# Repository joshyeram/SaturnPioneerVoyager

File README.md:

# Saturn with Pioneer and Voyager

link to the build video: https://www.youtube.com/watch?v=A1N8exJrTmQ

# Saturn

With this keyboard, I wanted to experiment with the possibility of hot-swappable keyboards. In the current state of using machine sockets and pins, no one dares to hot-swap. And I wanted to fix that and come up with a universal microcontroller daughter board that you can simply swap around.

# Pioneer

Pioneer is a simple daughterboard that supports a pro-micro-like microcontroller and a simple switch (reset). You can use qmk to program it.

# Voyager

Voyager is a complicated daughterboard that supports a pro-micro-like microcontroller, either oled or nice!view, a battery, and two switches (reset and power). Because of this, it is very thick to support all the hardware. In this case, I decided to use a Supermini for cost reasons. However, a genuine nice!nano should work as well. For programming, zmk was used for Bluetooth. 

# PCB

All you need is one pcb for all the boards. This is because I designed the daughter boards to be in the corners of the board to save manufacturing costs. This is at the cost of needing to score and snap off each board.

The reason why this works is because all the connections are standardized

Also, I think I got really lucky with the auditor not checking the thin mouse bite. so you may need to increase the tab if they do not except it.

# Firmware
I have already compiled and posted the .hex (qmk) and build.yaml(zmk) in the firmware folder. However, if you would like to make it your own, I have posted the full source code of what I used as well. (There may be some refactoring issues but I think I got most of them. Let me know if there is anything to fix)

# Parts
The most important part of the whole build was the DB25 connectors. I had to edit the existing DB25 footprint to fit my DB25 pins. So, you might have to as well.
Here is the list of parts I used
- pcb
- db25 connectors from amazon
- promicro 
- nice!nano clone
- nice!view from typeractive.xyz (they are great btw)
-  holy panda clones
- silent honey peaches
- 3 pin switches
- 1n4148 diodes
- uv resin
- some wire for cs pin
- keycaps (cerakeys w)

# anything else
please ask me anything if you guys want to! it is joshyeram on most platforms.

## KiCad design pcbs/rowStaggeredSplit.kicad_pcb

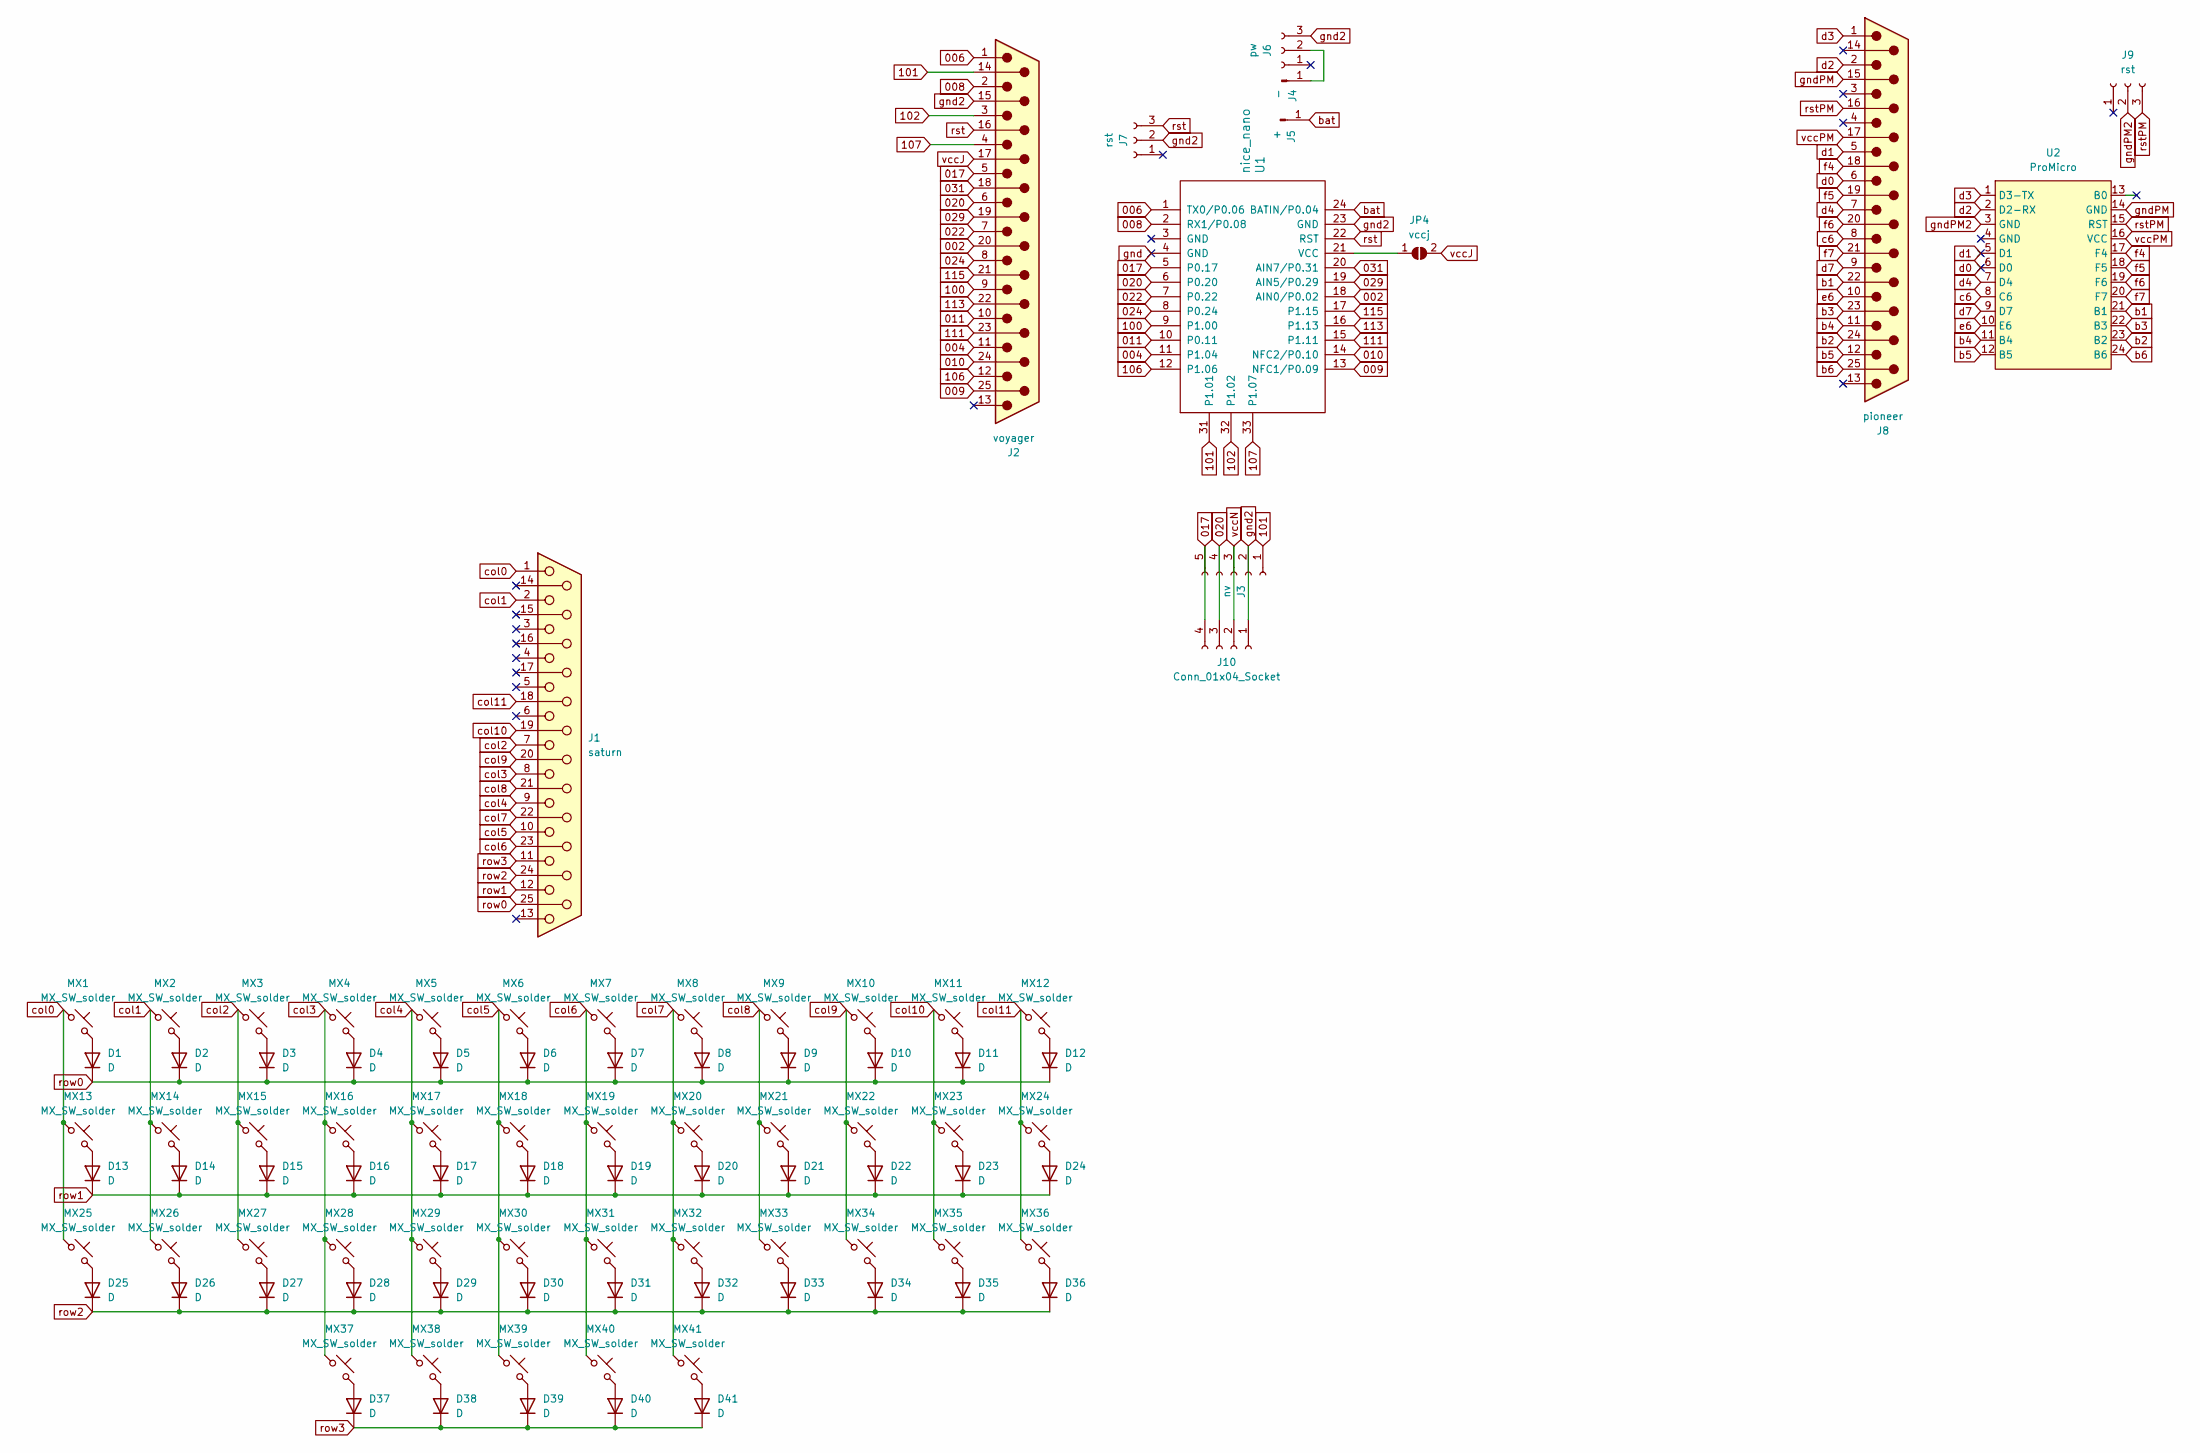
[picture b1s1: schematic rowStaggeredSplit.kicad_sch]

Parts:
D1, D2, D3, D4, D5, D6, D7, D8, D9, D10, D11, D12, D13, D14, D15, D16, D17, D18, D19, D20, D21, D22, D23, D24, D25, D26, D27, D28, D29, D30, D31, D32, D33, D34, D35, D36, D37, D38, D39, D40, D41: D; D_DO-35_SOD27_P7.62mm_Horizontal
J1: saturn; DSUB-25_Female_Vertical_P2.77x2.84mm2
J2: voyager; DSUB-25_Male_Vertical_P2.77x2.84mm2
J3: nv; PinSocket_1x05_P2.54mm_Vertical
J4: -; SolderWire-0.25sqmm_1x01_D0.65mm_OD2mm
J5: +; SolderWire-0.25sqmm_1x01_D0.65mm_OD2mm
J6: pw; PinSocket_1x03_P2.54mm_Vertical
J7, J9: rst; PinSocket_1x03_P2.54mm_Vertical
J8: pioneer; DSUB-25_Male_Vertical_P2.77x2.84mm2
J10: Conn_01x04_Socket; PinSocket_1x04_P2.54mm_Vertical
JP4: vccj; SolderJumper-2_P1.3mm_Open_TrianglePad1.0x1.5mm
MX1, MX2, MX3, MX4, MX5, MX6, MX7, MX8, MX9, MX10, MX11, MX14, MX15, MX16, MX17, MX18, MX19, MX20, MX21, MX22, MX23, MX26, MX27, MX28, MX29, MX30, MX31, MX32, MX33, MX34, MX35, MX36: MX_SW_solder; CherryMX_ChocV2_1u
MX12, MX25: MX_SW_solder; CherryMX_ChocV2_1.75u
MX13, MX37, MX38, MX39, MX40, MX41: MX_SW_solder; CherryMX_ChocV2_1.25u
MX24: MX_SW_solder; CherryMX_ChocV2_1.5u
U1: nice_nano
U2: ProMicro; ProMicro_USBup

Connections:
002: J2.20, U1.18 (AIN0/P0.02)
004: J2.11, U1.11 (P1.04)
006: J2.1, U1.1 (TX0/P0.06)
008: J2.2, U1.2 (RX1/P0.08)
009: J2.25, U1.13 (NFC1/P0.09)
010: J2.24, U1.14 (NFC2/P0.10)
011: J2.10, U1.10 (P0.11)
017: J2.5, J3.5, J10.4, U1.5 (P0.17)
020: J2.6, J3.4, J10.3, U1.6 (P0.20)
022: J2.7, U1.7 (P0.22)
024: J2.8, U1.8 (P0.24)
029: J2.19, U1.19 (AIN5/P0.29)
031: J2.18, U1.20 (AIN7/P0.31)
100: J2.9, U1.9 (P1.00)
101: J2.14, J3.1, U1.31 (P1.01)
102: J2.3, U1.32 (P1.02)
106: J2.12, U1.12 (P1.06)
107: J2.4, U1.33 (P1.07)
111: J2.23, U1.15 (P1.11)
113: J2.22, U1.16 (P1.13)
115: J2.21, U1.17 (P1.15)
unnamed: D1.2 (A), MX1.2
unnamed: D2.2 (A), MX2.2
unnamed: D3.2 (A), MX3.2
unnamed: D4.2 (A), MX4.2
unnamed: D5.2 (A), MX5.2
unnamed: D6.2 (A), MX6.2
unnamed: D7.2 (A), MX7.2
unnamed: D8.2 (A), MX8.2
unnamed: D9.2 (A), MX9.2
unnamed: D10.2 (A), MX10.2
unnamed: D11.2 (A), MX11.2
unnamed: D12.2 (A), MX12.2
unnamed: D13.2 (A), MX13.2
unnamed: D14.2 (A), MX14.2
unnamed: D15.2 (A), MX15.2
unnamed: D16.2 (A), MX16.2
unnamed: D17.2 (A), MX17.2
unnamed: D18.2 (A), MX18.2
unnamed: D19.2 (A), MX19.2
unnamed: D20.2 (A), MX20.2
unnamed: D21.2 (A), MX21.2
unnamed: D22.2 (A), MX22.2
unnamed: D23.2 (A), MX23.2
unnamed: D24.2 (A), MX24.2
unnamed: D25.2 (A), MX25.2
unnamed: D26.2 (A), MX26.2
unnamed: D27.2 (A), MX27.2
unnamed: D28.2 (A), MX28.2
unnamed: D29.2 (A), MX29.2
unnamed: D30.2 (A), MX30.2
unnamed: D31.2 (A), MX31.2
unnamed: D32.2 (A), MX32.2
unnamed: D33.2 (A), MX33.2
unnamed: D34.2 (A), MX34.2
unnamed: D35.2 (A), MX35.2
unnamed: D36.2 (A), MX36.2
unnamed: D37.2 (A), MX37.2
unnamed: D38.2 (A), MX38.2
unnamed: D39.2 (A), MX39.2
unnamed: D40.2 (A), MX40.2
unnamed: D41.2 (A), MX41.2
unnamed: J4.1, J6.2
unnamed: JP4.1 (A), U1.21 (VCC)
b1: J8.22, U2.21 (B1); also elsewhere on the board
b2: J8.24, U2.23 (B2); also elsewhere on the board
b3: J8.23, U2.22 (B3); also elsewhere on the board
b4: J8.11, U2.11 (B4); also elsewhere on the board
b5: J8.12, U2.12 (B5); also elsewhere on the board
b6: J8.25, U2.24 (B6); also elsewhere on the board
bat: J5.1, U1.24 (BATIN/P0.04)
c6: J8.8, U2.8 (C6); also elsewhere on the board
col0: J1.1, MX1.1, MX13.1, MX25.1
col1: J1.2, MX2.1, MX14.1, MX26.1
col2: J1.7, MX3.1, MX15.1, MX27.1
col3: J1.8, MX4.1, MX16.1, MX28.1, MX37.1
col4: J1.9, MX5.1, MX17.1, MX29.1, MX38.1
col5: J1.10, MX6.1, MX18.1, MX30.1, MX39.1
col6: J1.23, MX7.1, MX19.1, MX31.1, MX40.1
col7: J1.22, MX8.1, MX20.1, MX32.1, MX41.1
col8: J1.21, MX9.1, MX21.1, MX33.1
col9: J1.20, MX10.1, MX22.1, MX34.1
col10: J1.19, MX11.1, MX23.1, MX35.1
col11: J1.18, MX12.1, MX24.1, MX36.1
d0: J8.6, U2.6 (D0); also elsewhere on the board
d1: J8.5, U2.5 (D1); also elsewhere on the board
d2: J8.2, U2.2 (D2-RX); also elsewhere on the board
d3: J8.1, U2.1 (D3-TX); also elsewhere on the board
d4: J8.7, U2.7 (D4); also elsewhere on the board
d7: J8.9, U2.9 (D7); also elsewhere on the board
e6: J8.10, U2.10 (E6); also elsewhere on the board
f4: J8.18, U2.17 (F4); also elsewhere on the board
f5: J8.19, U2.18 (F5); also elsewhere on the board
f6: J8.20, U2.19 (F6); also elsewhere on the board
f7: J8.21, U2.20 (F7); also elsewhere on the board
gnd: U1.4 (GND)
gnd2: J2.15, J3.2, J6.3, J7.2, J10.1, U1.23 (GND)
gndPM: J8.15, U2.14 (GND); also elsewhere on the board
gndPM2: J9.2, U2.3 (GND)
row0: D1.1 (K), D2.1 (K), D3.1 (K), D4.1 (K), D5.1 (K), D6.1 (K), D7.1 (K), D8.1 (K), D9.1 (K), D10.1 (K), D11.1 (K), D12.1 (K), J1.25
row1: D13.1 (K), D14.1 (K), D15.1 (K), D16.1 (K), D17.1 (K), D18.1 (K), D19.1 (K), D20.1 (K), D21.1 (K), D22.1 (K), D23.1 (K), D24.1 (K), J1.12
row2: D25.1 (K), D26.1 (K), D27.1 (K), D28.1 (K), D29.1 (K), D30.1 (K), D31.1 (K), D32.1 (K), D33.1 (K), D34.1 (K), D35.1 (K), D36.1 (K), J1.24
row3: D37.1 (K), D38.1 (K), D39.1 (K), D40.1 (K), D41.1 (K), J1.11
rst: J2.16, J7.3, U1.22 (RST)
rstPM: J8.16, J9.3, U2.15 (RST); also elsewhere on the board
vccJ: J2.17, JP4.2 (B)
vccN: J3.3, J10.2
vccPM: J8.17, U2.16 (VCC); also elsewhere on the board

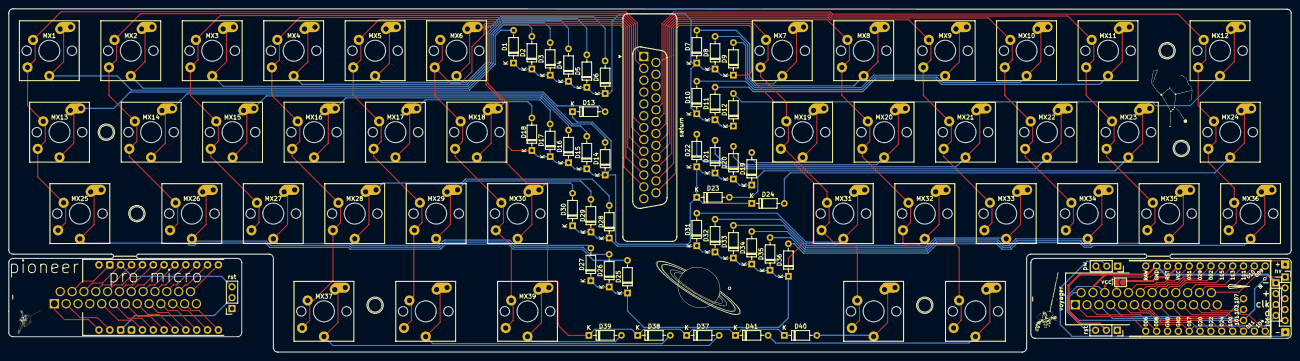
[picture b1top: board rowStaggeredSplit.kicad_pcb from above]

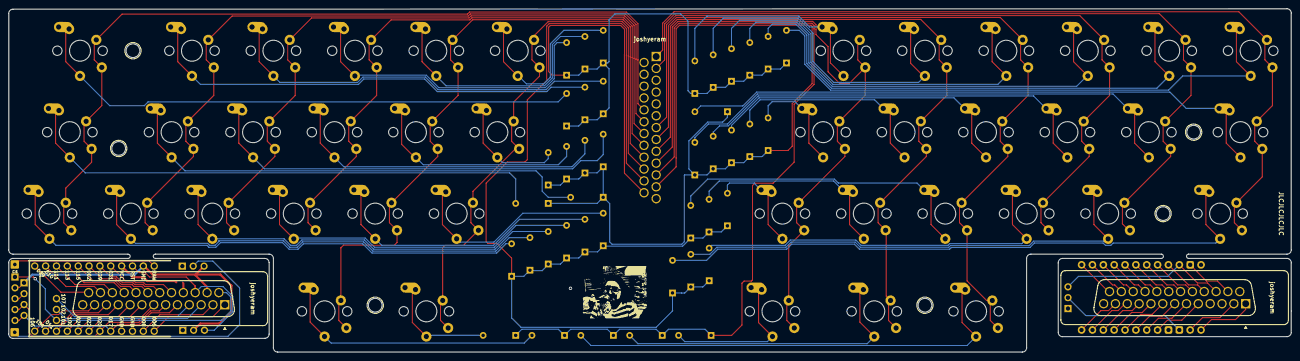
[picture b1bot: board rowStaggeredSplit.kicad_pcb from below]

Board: 2 copper layers, 300.0 x 80.3 mm, 96 parts (2 on the bottom side), 107 nets.

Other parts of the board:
Ge: LOGO; jor
locked: titan; DSUB-25_Male_Vertical_P2.77x2.84mm2

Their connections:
b1: locked.22; also elsewhere on the board
b2: locked.24; also elsewhere on the board
b3: locked.23; also elsewhere on the board
b4: locked.11; also elsewhere on the board
b5: locked.12; also elsewhere on the board
b6: locked.25; also elsewhere on the board
c6: locked.8; also elsewhere on the board
d0: locked.6; also elsewhere on the board
d1: locked.5; also elsewhere on the board
d2: locked.2; also elsewhere on the board
d3: locked.1; also elsewhere on the board
d4: locked.7; also elsewhere on the board
d7: locked.9; also elsewhere on the board
e6: locked.10; also elsewhere on the board
f4: locked.18; also elsewhere on the board
f5: locked.19; also elsewhere on the board
f6: locked.20; also elsewhere on the board
f7: locked.21; also elsewhere on the board
gndPM: locked.15; also elsewhere on the board
rstPM: locked.16; also elsewhere on the board
vccPM: locked.17; also elsewhere on the board

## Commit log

2024-01-08 SaturnPioneerVoyager
2024-01-08 Reorganize
